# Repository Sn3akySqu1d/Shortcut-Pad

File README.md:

Shortcut pad is a 6 key layered macropad. You can switch between layers using the last key. the layers contain different macros.

Schematic:  
  
PCB:  

BOM:  
XIAO RP2040 (1)  
SK6812 MINI-E LEDs (6)  
MX-Style switches (6)  
M3x16mm screws (4)  
3d printed case (top and bottom)  

demo: https://www.reddit.com/user/Huge_Cartoonist5504/comments/1m5prar/shortcut_macropad/
[submitted before yt was a requirement so there isnt one linked on the form]

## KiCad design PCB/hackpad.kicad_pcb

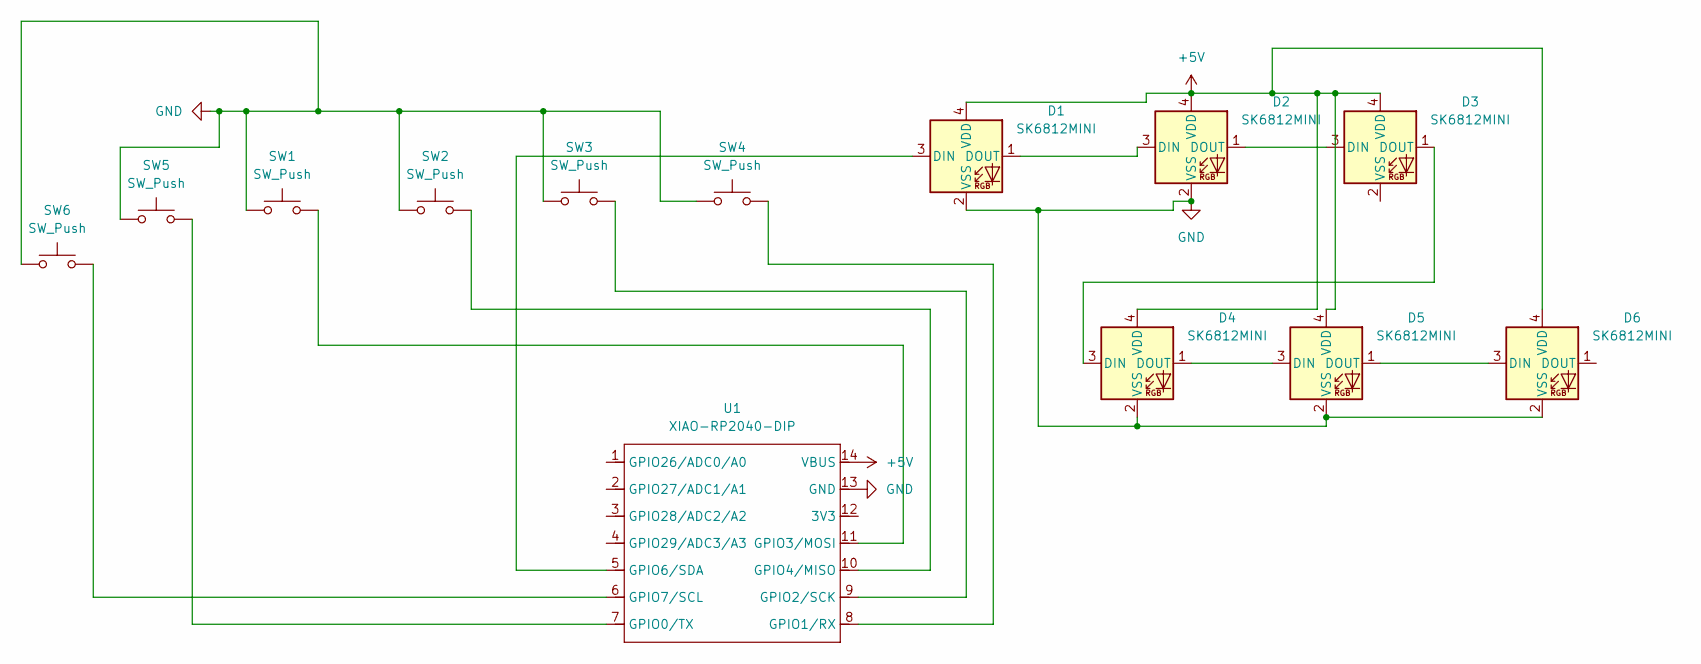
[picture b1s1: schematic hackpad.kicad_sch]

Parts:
D1, D2, D3, D4, D5, D6: SK6812MINI; LED_SK6812MINI_PLCC4_3.5x3.5mm_P1.75mm
SW1, SW2, SW3, SW4, SW5, SW6: SW_Push; SW_Cherry_MX_1.00u_PCB
U1: XIAO-RP2040-DIP

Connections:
+5V: D1.4 (VDD), D2.4 (VDD), D3.4 (VDD), D4.4 (VDD), D5.4 (VDD), D6.4 (VDD), U1.14 (VBUS)
GND: D1.2 (VSS), D2.2 (VSS), D4.2 (VSS), D5.2 (VSS), D6.2 (VSS), SW1.1, SW2.1, SW3.1, SW4.1, SW5.1, SW6.1, U1.13 (GND)
unnamed: D1.3 (DIN), U1.5 (GPIO6/SDA)
unnamed: D1.1 (DOUT), D2.3 (DIN)
unnamed: D2.1 (DOUT), D3.3 (DIN)
unnamed: D3.1 (DOUT), D4.3 (DIN)
unnamed: D4.1 (DOUT), D5.3 (DIN)
unnamed: D5.1 (DOUT), D6.3 (DIN)
unnamed: SW5.2, U1.7 (GPIO0/TX)
unnamed: SW4.2, U1.8 (GPIO1/RX)
unnamed: SW3.2, U1.9 (GPIO2/SCK)
unnamed: SW1.2, U1.11 (GPIO3/MOSI)
unnamed: SW2.2, U1.10 (GPIO4/MISO)
unnamed: SW6.2, U1.6 (GPIO7/SCL)

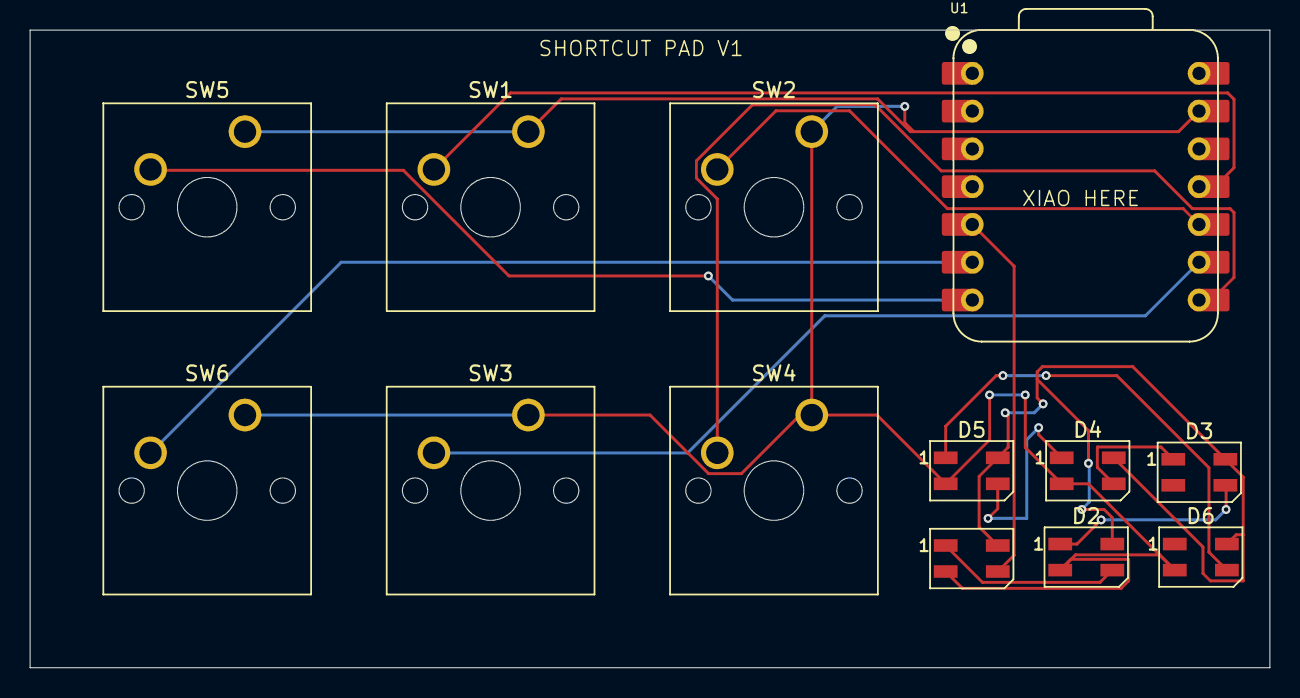
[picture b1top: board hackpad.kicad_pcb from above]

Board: 2 copper layers, 83.3 x 42.9 mm, 13 parts (0 on the bottom side), 14 nets.

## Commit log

2025-06-26 added files
2025-06-26 final commit
2025-06-27 updated silkscreen
2025-07-21 demo
